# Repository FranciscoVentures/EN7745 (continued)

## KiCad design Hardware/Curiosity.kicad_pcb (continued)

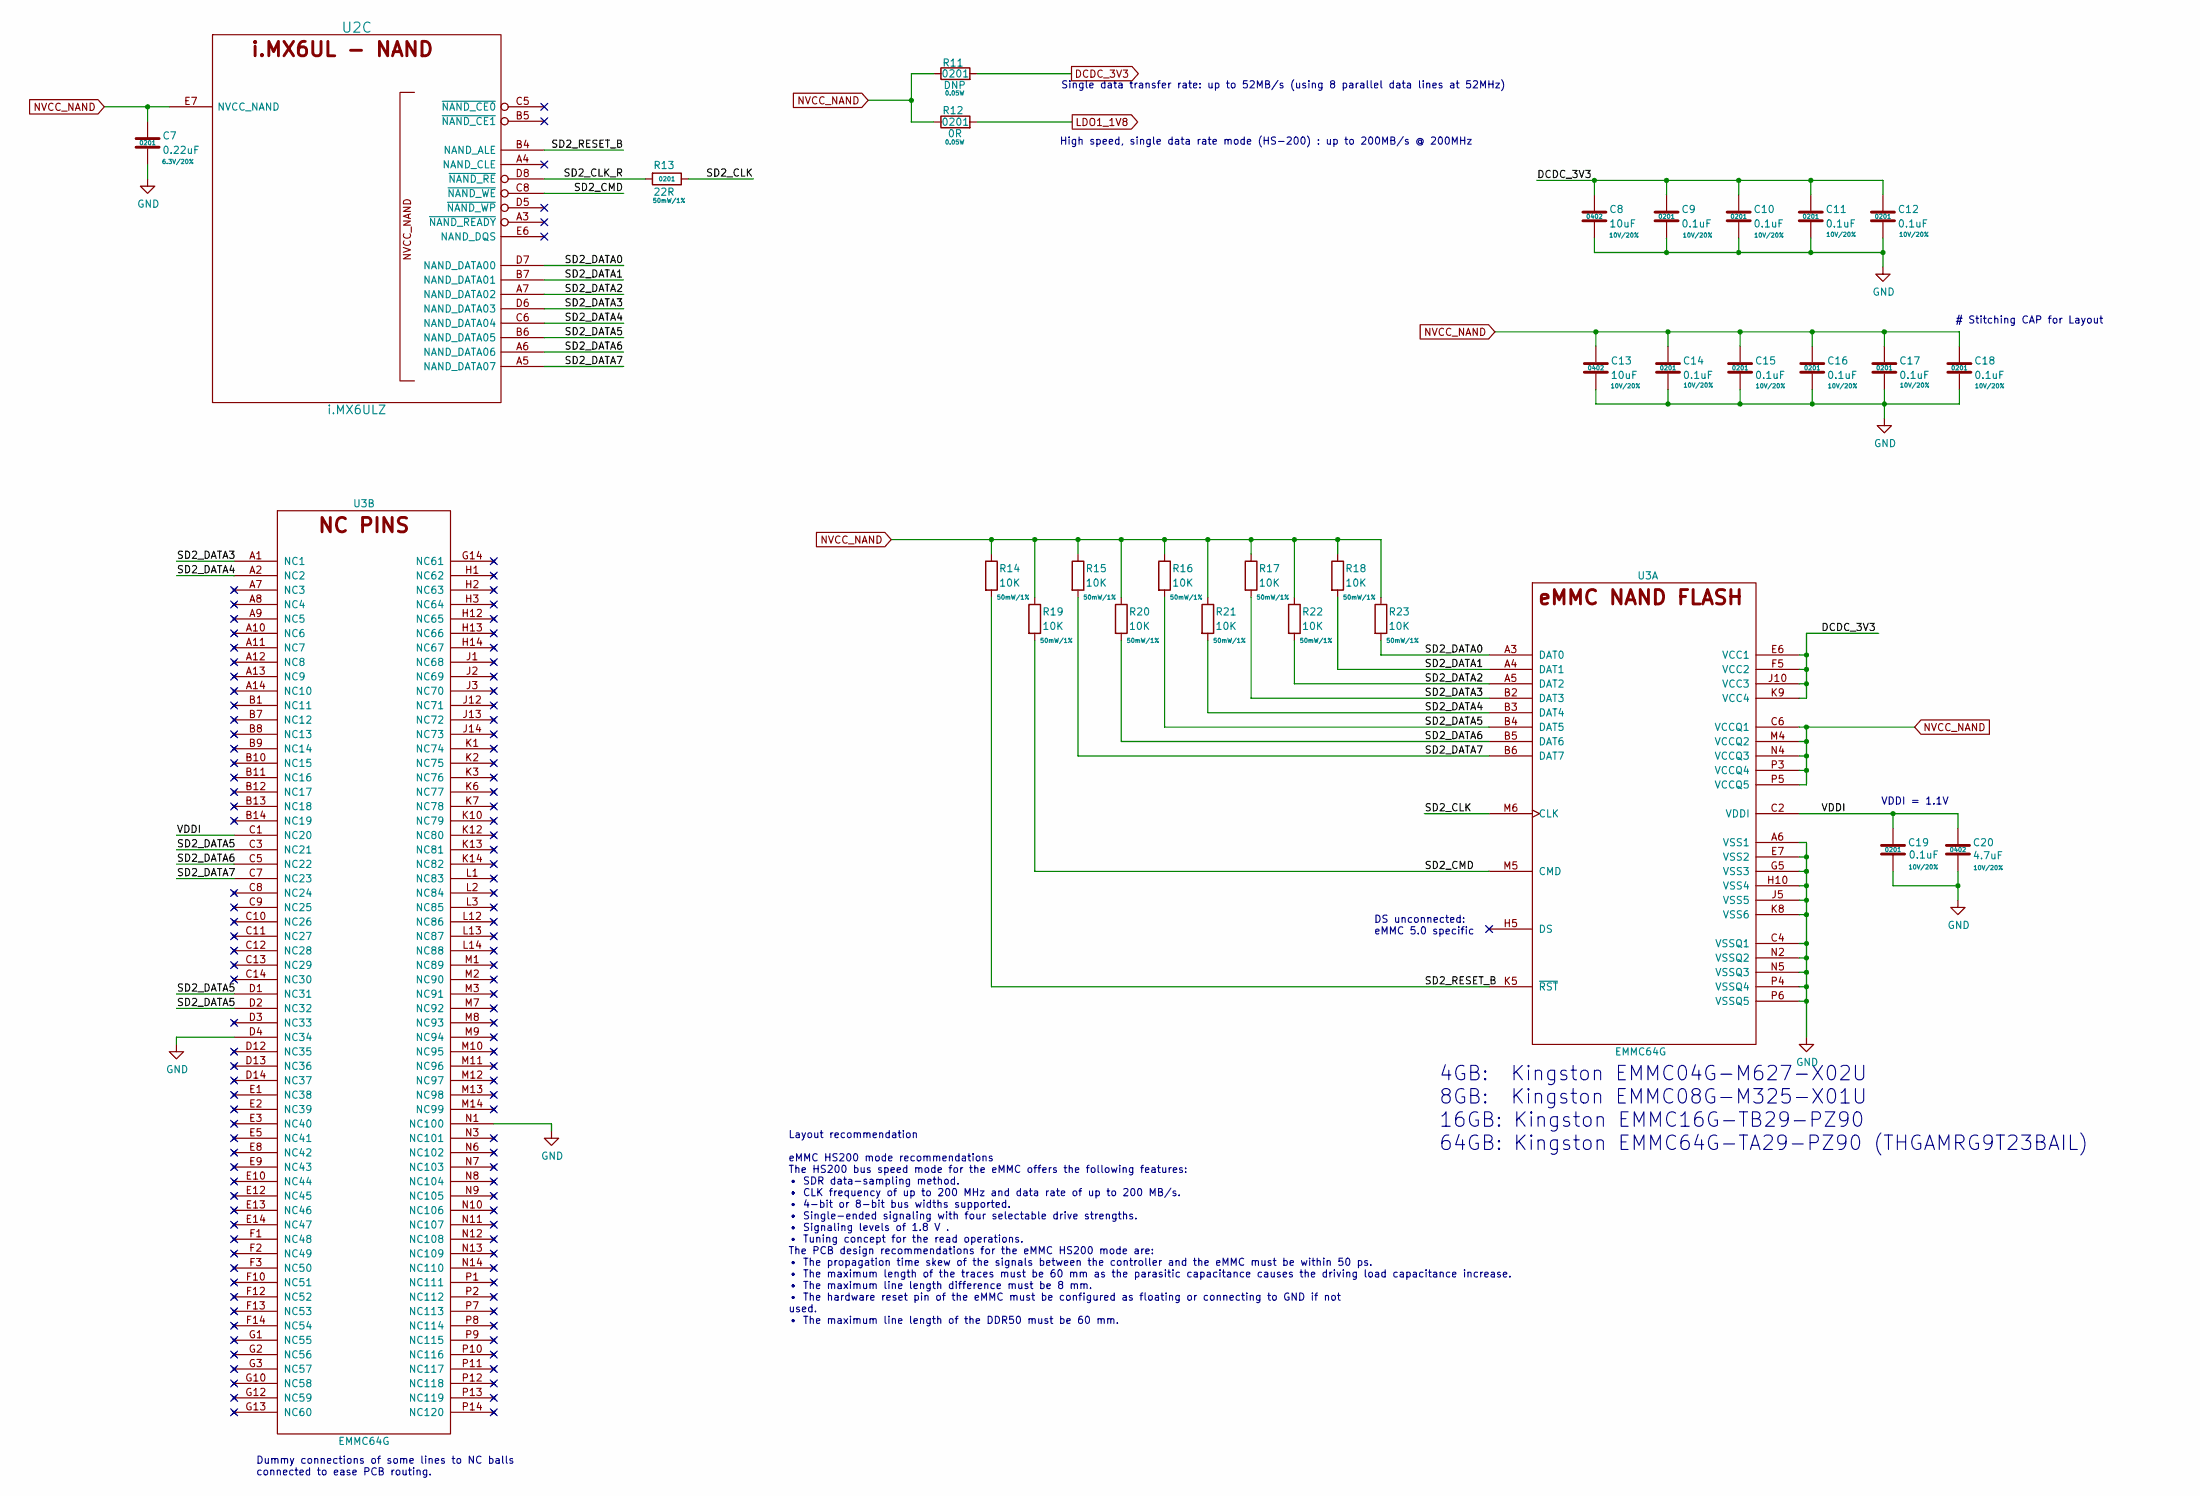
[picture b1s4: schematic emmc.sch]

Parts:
C7: 0.22uF; SM0201; Rating 6.3V/20%; Mfg PN GRM033R60J224ME15D; Digi-Key_PN 490-10407-1-ND
C8, C13: 10uF; SM0402; Rating 10V/20%; Mfg PN CL05A106MP8NUB8; Digi-Key_PN 1276-6830-1-ND
C9, C10, C11, C12, C14, C15, C16, C17, C18, C19: 0.1uF; SM0201; Rating 10V/20%; Mfg PN GRM033R61A104ME15D; Digi-Key_PN 490-5405-1-ND
C20: 4.7uF; SM0402; Rating 10V/20%; Mfg PN ZRB15XR61A475ME01D; Digi-Key_PN 490-10984-1-ND
R11: DNP; R_0201_0603Metric; Rating 0.05W; Mfg PN CRCW02010000Z0ED; Digi-Key_PN 541-0.0AGCT-ND
R12: 0R; R_0201_0603Metric; Rating 0.05W; Mfg PN CRCW02010000Z0ED; Digi-Key_PN 541-0.0AGCT-ND
R13: 22R; R_0201_0603Metric; Rating 50mW/1%; Mfg PN CRCW020122R0JNED; Digi-Key_PN 541-22AGCT-ND
R14, R15, R16, R17, R18, R19, R20, R21, R22, R23: 10K; R_0201_0603Metric; Rating 50mW/1%; Mfg PN CRCW020110K0JNED; Digi-Key_PN 541-10KAGCT-ND
U2: i.MX6ULZ; SOT1534-2; Mfg PN MCIMX6Z0DVM09AB; Digi-Key_PN 568-14726-ND
U3: EMMC64G; FBGA-153; Mfg PN THGAMRG9T23BAIL; Digi-Key_PN THGAMRG9T23BAIL-ND

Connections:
/eMMC/SD2_CLK: R13.1, U3.M6 (CLK)
/eMMC/SD2_CLK_R: R13.2, U2.D8 (~NAND_RE); also elsewhere on the board
/eMMC/SD2_CMD: R19.2, U2.C8 (~NAND_WE), U3.M5 (CMD); also elsewhere on the board
/eMMC/SD2_DATA0: R23.2, U2.D7 (NAND_DATA00), U3.A3 (DAT0); also elsewhere on the board
/eMMC/SD2_DATA1: R18.2, U2.B7 (NAND_DATA01), U3.A4 (DAT1); also elsewhere on the board
/eMMC/SD2_DATA2: R22.2, U2.A7 (NAND_DATA02), U3.A5 (DAT2); also elsewhere on the board
/eMMC/SD2_DATA3: R17.2, U2.D6 (NAND_DATA03), U3.A1 (NC1), U3.B2 (DAT3); also elsewhere on the board
/eMMC/SD2_DATA4: R21.2, U2.C6 (NAND_DATA04), U3.A2 (NC2), U3.B3 (DAT4); also elsewhere on the board
/eMMC/SD2_DATA5: R16.2, U2.B6 (NAND_DATA05), U3.B4 (DAT5), U3.C3 (NC21), U3.D1 (NC31), U3.D2 (NC32); also elsewhere on the board
/eMMC/SD2_DATA6: R20.2, U2.A6 (NAND_DATA06), U3.B5 (DAT6), U3.C5 (NC22); also elsewhere on the board
/eMMC/SD2_DATA7: R15.2, U2.A5 (NAND_DATA07), U3.B6 (DAT7), U3.C7 (NC23); also elsewhere on the board
/eMMC/SD2_RESET_B: R14.2, U2.B4 (NAND_ALE), U3.K5 (~RST); also elsewhere on the board
/eMMC/VDDI: C19.1, C20.1, U3.C1 (NC20), U3.C2 (VDDI)
DCDC_3V3: C8.1, C9.1, C10.1, C11.1, C12.1, R11.2, U3.E6 (VCC1), U3.F5 (VCC2), U3.J10 (VCC3), U3.K9 (VCC4); also elsewhere on the board
GND: C7.2, C8.2, C9.2, C10.2, C11.2, C12.2, C13.2, C14.2, C15.2, C16.2, C17.2, C18.2, C19.2, C20.2, U3.A6 (VSS1), U3.C4 (VSSQ1), U3.D4 (NC34), U3.E7 (VSS2), U3.G5 (VSS3), U3.H10 (VSS4), U3.J5 (VSS5), U3.K8 (VSS6), U3.N1 (NC100), U3.N2 (VSSQ2), U3.N5 (VSSQ3), U3.P4 (VSSQ4), U3.P6 (VSSQ5); also elsewhere on the board
LDO1_1V8: R12.2; also elsewhere on the board
NVCC_NAND: C7.1, C13.1, C14.1, C15.1, C16.1, C17.1, C18.1, R11.1, R12.1, R14.1, R15.1, R16.1, R17.1, R18.1, R19.1, R20.1, R21.1, R22.1, R23.1, U2.E7 (NVCC_NAND), U3.C6 (VCCQ1), U3.M4 (VCCQ2), U3.N4 (VCCQ3), U3.P3 (VCCQ4), U3.P5 (VCCQ5); also elsewhere on the board
unnamed 175: U2.A3 (~NAND_READY); also elsewhere on the board
unnamed 176: U2.A4 (NAND_CLE); also elsewhere on the board
unnamed 182: U2.B5 (~NAND_CE1); also elsewhere on the board
unnamed 187: U2.C5 (~NAND_CE0); also elsewhere on the board
unnamed 192: U2.D5 (~NAND_WP); also elsewhere on the board
unnamed 196: U2.E6 (NAND_DQS); also elsewhere on the board

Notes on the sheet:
Dummy connections of some lines to NC balls connected to ease PCB routing.
DS unconnected: eMMC 5.0 specific
4GB: Kingston EMMC04G-M627-X02U 8GB: Kingston EMMC08G-M325-X01U 16GB: Kingston EMMC16G-TB29-PZ90 64GB: Kingston EMMC64G-TA29-PZ90 (THGAMRG9T23BAIL)
# Stitching CAP for Layout
High speed, single data rate mode (HS-200) : up to 200MB/s @ 200MHz
Single data transfer rate: up to 52MB/s (using 8 parallel data lines at 52MHz)
Layout recommendation eMMC HS200 mode recommendations The HS200 bus speed mode for the eMMC offers the following features: • SDR data-sampling method. • CLK frequency of up to 200 MHz and data rate of up to 200 MB/s. • 4-bit or 8-bit bus widths supported. • Single-ended signaling with four selectab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
VDDI = 1.1V

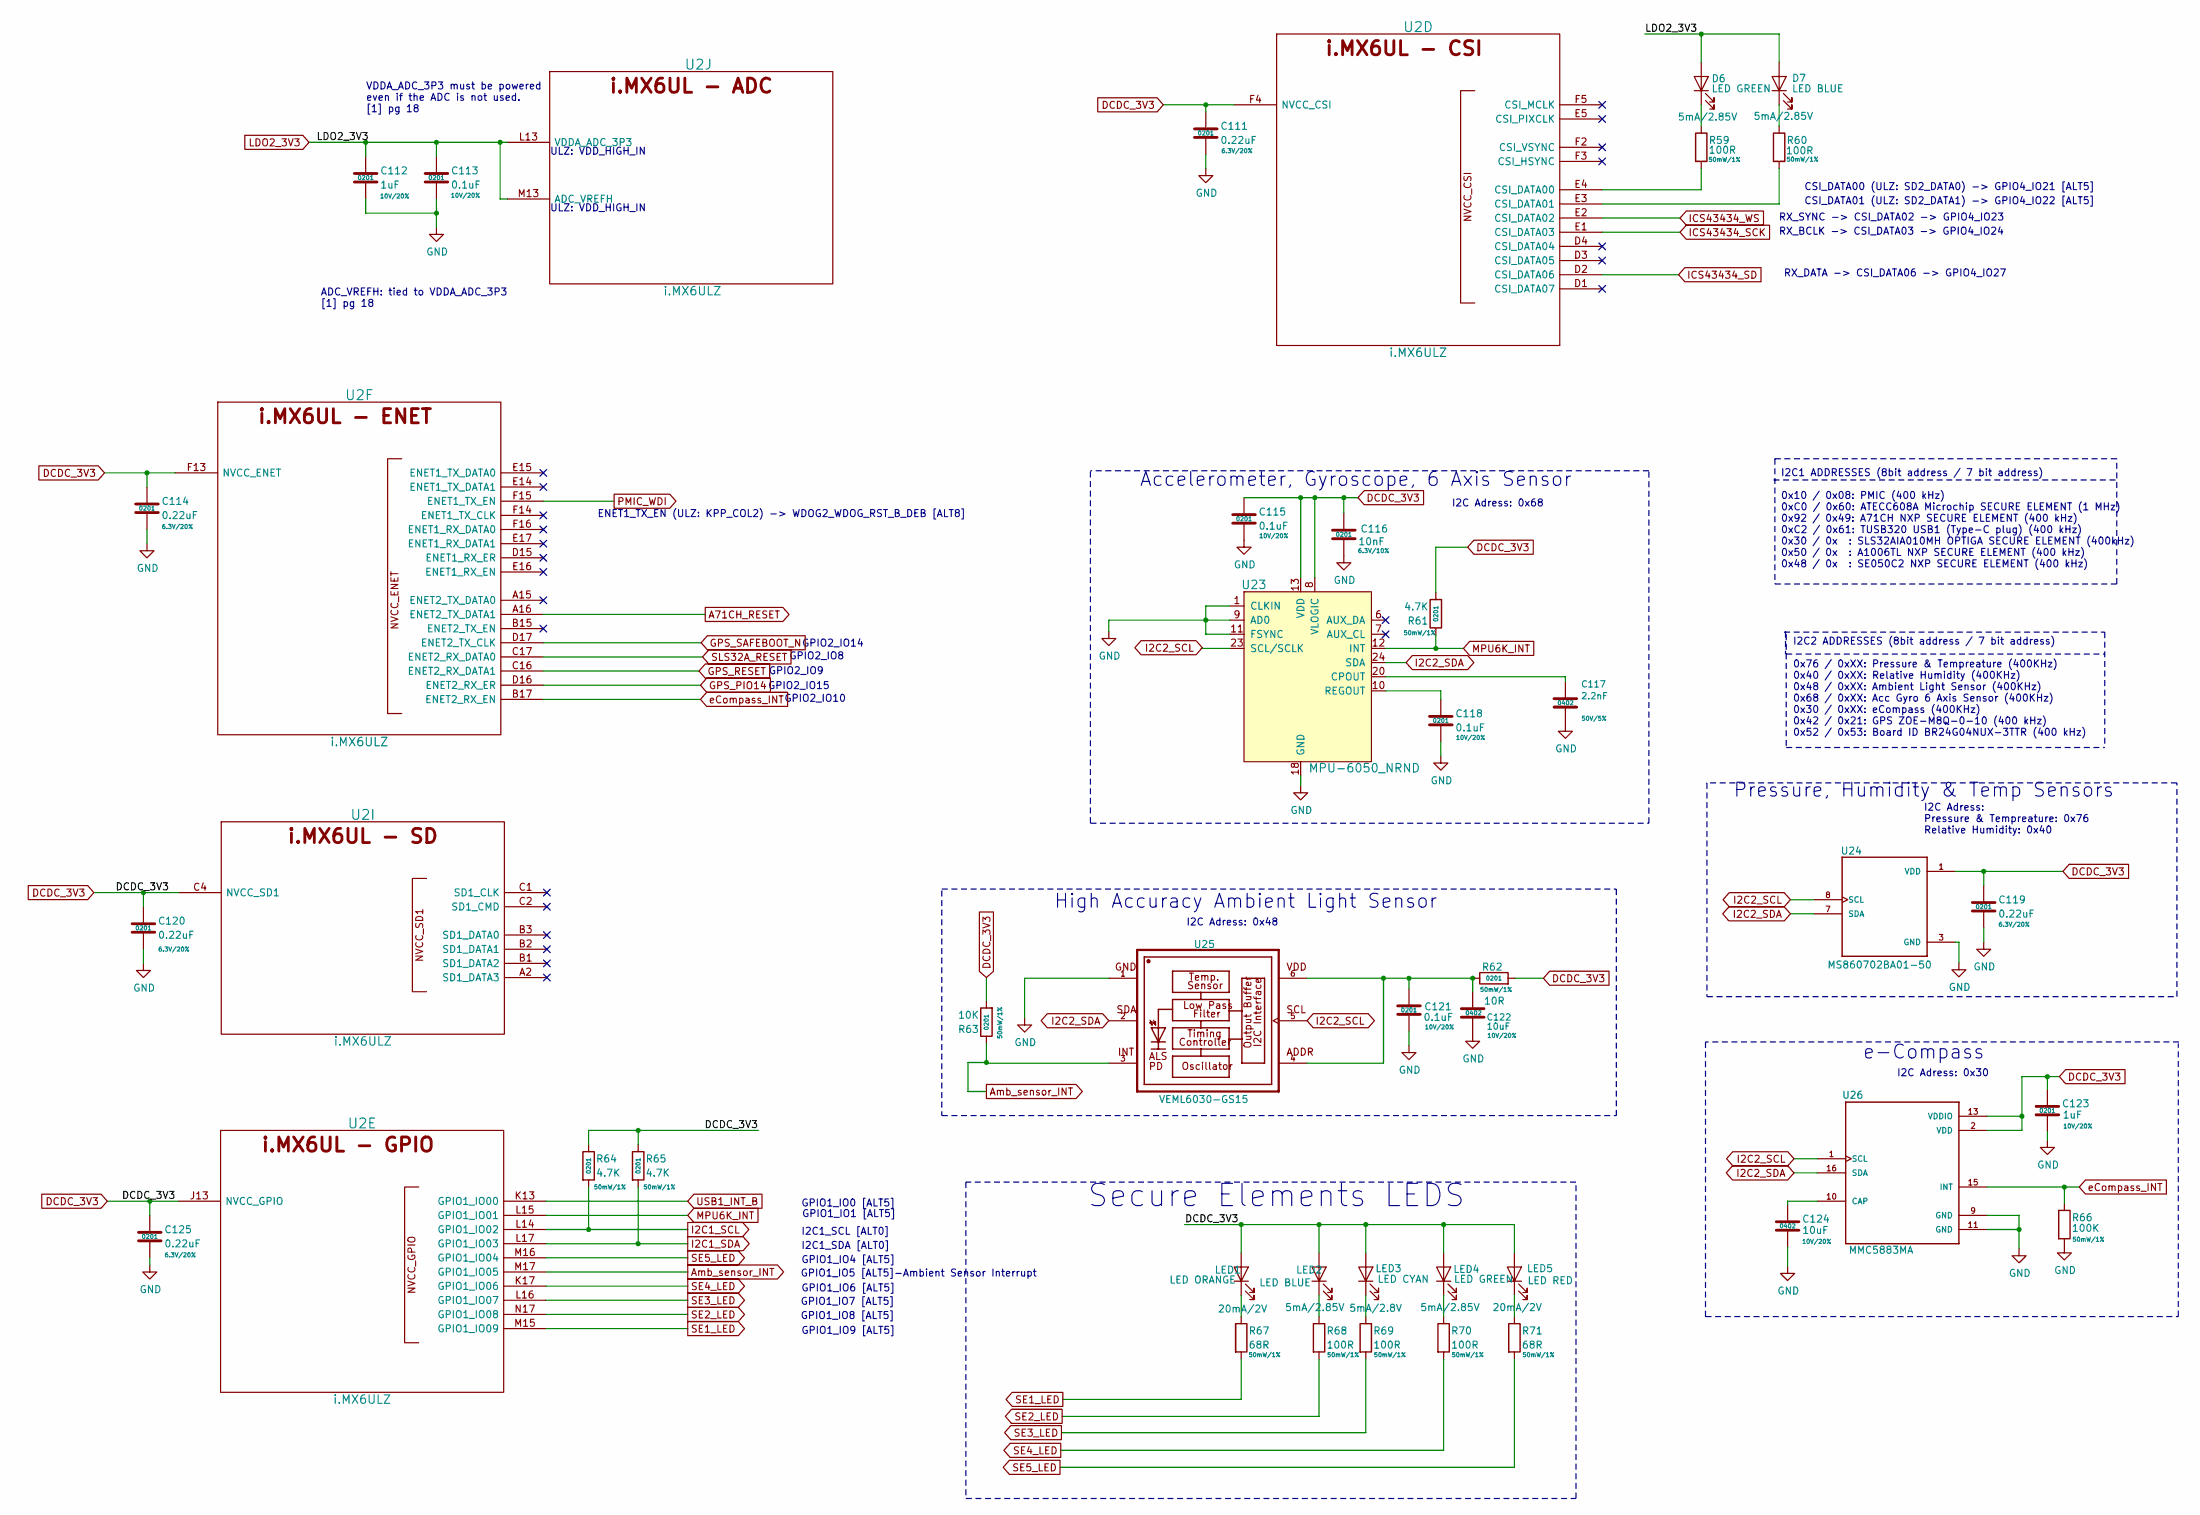
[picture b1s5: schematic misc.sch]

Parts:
C111, C114, C119, C120, C125: 0.22uF; SM0201; Rating 6.3V/20%; Mfg PN GRM033R60J224ME15D; Digi-Key_PN 490-10407-1-ND
C112, C123: 1uF; SM0201; Rating 10V/20%; Mfg PN CL03A105MP3ZSNH; Digi-Key_PN 1276-6816-1-ND
C113, C115, C118, C121: 0.1uF; SM0201; Rating 10V/20%; Mfg PN GRM033R61A104ME15D; Digi-Key_PN 490-5405-1-ND
C116: 10nF; SM0201; Rating 6.3V/10%; Mfg PN GRM033R70J103KA01D; Digi-Key_PN 490-1262-1-ND
C117: 2.2nF; C_0402_1005Metric; Rating 50V/5%; Mfg PN GRM155R71H222JA01J; Digi-Key_PN 490-6359-1-ND
C122: 10uF; C_0402_1005Metric; Rating 10V/20%; Mfg PN CL05A106MP8NUB8; Digi-Key_PN 1276-6830-1-ND
C124: 10uF; SM0402; Rating 10V/20%; Mfg PN CL05A106MP8NUB8; Digi-Key_PN 1276-6830-1-ND
D6: LED GREEN; LED_0603; Rating 5mA/2.85V; Mfg PN LT Q39G-Q1OO-25-1; Digi-Key_PN 475-3442-1-ND
D7: LED BLUE; SM0603_LED; Rating 5mA/2.85V; Mfg PN LB Q39G-L2OO-35-1; Digi-Key_PN 475-2816-1-ND
LED1: LED ORANGE; LED_0603; Rating 20mA/2V; Mfg PN LO Q976-PS-25-0-20-R18; Digi-Key_PN 475-2486-1-ND
LED2: LED BLUE; LED_0603; Rating 5mA/2.85V; Mfg PN LB Q39G-L2OO-35-1; Digi-Key_PN 475-2816-1-ND
LED3: LED CYAN; LED_0603; Rating 5mA/2.8V; Mfg PN APT1608VRCXF/A-5MAV; Digi-Key_PN 754-2180-1-ND
LED4: LED GREEN; LED_0603; Rating 5mA/2.85V; Mfg PN LT Q39G-Q1OO-25-1; Digi-Key_PN 475-3442-1-ND
LED5: LED RED; LED_0603; Rating 20mA/2V; Mfg PN LS Q976-NR-1; Digi-Key_PN 475-2512-1-ND
R59, R60, R68, R69, R70: 100R; R_0201_0603Metric; Rating 50mW/1%; Mfg PN CRCW0201100RFNED; Digi-Key_PN 541-100ABCT-ND
R61, R64, R65: 4.7K; R_0201_0603Metric; Rating 50mW/1%; Mfg PN CRCW02014K70JNED; Digi-Key_PN 541-4.7KAGCT-ND
R62: 10R; R_0201_0603Metric; Rating 50mW/1%; Mfg PN CRCW020110R0FNED; Digi-Key_PN 541-10.0ABCT-ND
R63: 10K; R_0201_0603Metric; Rating 50mW/1%; Mfg PN CRCW020110K0JNED; Digi-Key_PN 541-10KAGCT-ND
R66: 100K; R_0201_0603Metric; Rating 50mW/1%; Mfg PN CRCW0201100KJNED; Digi-Key_PN 541-100KAGCT-ND
R67, R71: 68R; R_0201_0603Metric; Rating 50mW/1%; Mfg PN CRCW020168R0FNED; Digi-Key_PN 541-CRCW020168R0FNEDCT-ND
U2: i.MX6ULZ; SOT1534-2; Mfg PN MCIMX6Z0DVM09AB; Digi-Key_PN 568-14726-ND
U23: MPU-6050_NRND; QFN-24-1EP_4x4mm; Mfg PN MPU-6050; Digi-Key_PN 1428-1007-1-ND
U24: MS860702BA01-50; TE_MS860702BA01-50; Mfg PN MS860702BA01-50; Digi-Key_PN 223-1701-1-ND
U25: VEML6030-GS15; VISHAY_VEML6030_2X2X0.87; Mfg PN VEML6030-GS15; Digi-Key_PN VEML6030-GS15CT-ND
U26: MMC5883MA; PQFN50P300X300X100-16N; Mfg PN MMC5883MA; Digi-Key_PN 1267-1072-1-ND

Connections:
A71CH_RESET: U2.A16 (ENET2_TX_DATA1); also elsewhere on the board
Amb_sensor_INT: R63.1, U2.M17 (GPIO1_IO05), U25.3; also elsewhere on the board
DCDC_3V3: C111.1, C114.1, C115.1, C116.1, C119.1, C120.1, C123.1, C125.1, LED1.2 (A), LED2.2 (A), LED3.2 (A), LED4.2 (A), LED5.2 (A), R61.2, R62.2, R63.2, R64.1, R65.1, U2.C4 (NVCC_SD1), U2.F4 (NVCC_CSI), U2.F13 (NVCC_ENET), U2.J13 (NVCC_GPIO), U23.8 (VLOGIC), U23.13 (VDD), U24.1 (VDD), U26.2 (VDD), U26.13 (VDDIO); also elsewhere on the board
GND: C111.2, C112.2, C113.2, C114.2, C115.2, C116.2, C117.2, C118.2, C119.2, C120.2, C121.2, C122.2, C123.2, C124.2, C125.2, R66.2, U23.1 (CLKIN), U23.9 (AD0), U23.11 (FSYNC), U23.18 (GND), U24.3 (GND), U25.1, U26.9 (GND), U26.11 (GND); also elsewhere on the board
GPS_PIO14: U2.D16 (ENET2_RX_ER); also elsewhere on the board
GPS_RESET: U2.C16 (ENET2_RX_DATA1); also elsewhere on the board
GPS_SAFEBOOT_N: U2.D17 (ENET2_TX_CLK); also elsewhere on the board
I2C1_SCL: R64.2, U2.L14 (GPIO1_IO02); also elsewhere on the board
I2C1_SDA: R65.2, U2.L17 (GPIO1_IO03); also elsewhere on the board
I2C2_SCL: U23.23 (SCL/SCLK), U24.8 (SCL), U25.5, U26.1 (SCL); also elsewhere on the board
I2C2_SDA: U23.24 (SDA), U24.7 (SDA), U25.2, U26.16 (SDA); also elsewhere on the board
ICS43434_SCK: U2.E1 (CSI_DATA03); also elsewhere on the board
ICS43434_SD: U2.D2 (CSI_DATA06); also elsewhere on the board
ICS43434_WS: U2.E2 (CSI_DATA02); also elsewhere on the board
LDO2_3V3: C112.1, C113.1, D6.2 (A), D7.2 (A), U2.L13 (VDDA_ADC_3P3), U2.M13 (ADC_VREFH); also elsewhere on the board
MPU6K_INT: R61.1, U2.L15 (GPIO1_IO01), U23.12 (INT); also elsewhere on the board
unnamed: C117.1, U23.20 (CPOUT)
unnamed: C118.1, U23.10 (REGOUT)
unnamed: C121.1, C122.1, R62.1, U25.4, U25.6
unnamed: C124.1, U26.10 (CAP)
unnamed: D6.1 (K), R59.1
unnamed: D7.1 (K), R60.1
unnamed: LED1.1 (K), R67.1
unnamed: LED2.1 (K), R68.1
unnamed: LED3.1 (K), R69.1
unnamed: LED4.1 (K), R70.1
unnamed: LED5.1 (K), R71.1
unnamed 172: R59.2, U2.E4 (CSI_DATA00); also elsewhere on the board
unnamed 173: R60.2, U2.E3 (CSI_DATA01); also elsewhere on the board
unnamed 174: U2.A2 (SD1_DATA3); also elsewhere on the board
unnamed 178: U2.A15 (ENET2_TX_DATA0); also elsewhere on the board
unnamed 179: U2.B1 (SD1_DATA2); also elsewhere on the board
unnamed 180: U2.B2 (SD1_DATA1); also elsewhere on the board
unnamed 181: U2.B3 (SD1_DATA0); also elsewhere on the board
unnamed 184: U2.B15 (ENET2_TX_EN); also elsewhere on the board
unnamed 185: U2.C1 (SD1_CLK); also elsewhere on the board
unnamed 186: U2.C2 (SD1_CMD); also elsewhere on the board
unnamed 189: U2.D1 (CSI_DATA07); also elsewhere on the board
unnamed 190: U2.D3 (CSI_DATA05); also elsewhere on the board
unnamed 191: U2.D4 (CSI_DATA04); also elsewhere on the board
unnamed 194: U2.D15 (ENET1_RX_ER); also elsewhere on the board
unnamed 195: U2.E5 (CSI_PIXCLK); also elsewhere on the board
unnamed 198: U2.E14 (ENET1_TX_DATA1); also elsewhere on the board
unnamed 199: U2.E15 (ENET1_TX_DATA0); also elsewhere on the board
unnamed 200: U2.E16 (ENET1_RX_EN); also elsewhere on the board
unnamed 201: U2.E17 (ENET1_RX_DATA1); also elsewhere on the board
unnamed 203: U2.F2 (CSI_VSYNC); also elsewhere on the board
unnamed 204: U2.F3 (CSI_HSYNC); also elsewhere on the board
unnamed 205: U2.F5 (CSI_MCLK); also elsewhere on the board
unnamed 206: U2.F14 (ENET1_TX_CLK); also elsewhere on the board
unnamed 207: U2.F16 (ENET1_RX_DATA0); also elsewhere on the board
PMIC_WDI: U2.F15 (ENET1_TX_EN); also elsewhere on the board
SE1_LED: R67.2, U2.M15 (GPIO1_IO09); also elsewhere on the board
SE2_LED: R68.2, U2.N17 (GPIO1_IO08); also elsewhere on the board
SE3_LED: R69.2, U2.L16 (GPIO1_IO07); also elsewhere on the board
SE4_LED: R70.2, U2.K17 (GPIO1_IO06); also elsewhere on the board
SE5_LED: R71.2, U2.M16 (GPIO1_IO04); also elsewhere on the board
SLS32A_RESET: U2.C17 (ENET2_RX_DATA0); also elsewhere on the board
USB1_INT_B: U2.K13 (GPIO1_IO00); also elsewhere on the board
eCompass_INT: R66.1, U2.B17 (ENET2_RX_EN), U26.15 (INT); also elsewhere on the board

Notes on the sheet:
ADC_VREFH: tied to VDDA_ADC_3P3 [1] pg 18
VDDA_ADC_3P3 must be powered even if the ADC is not used. [1] pg 18
I2C1_SCL [ALT0]
I2C1_SDA [ALT0]
GPIO1_IO9 [ALT5]
GPIO1_IO6 [ALT5]
GPIO1_IO4 [ALT5]
I2C1 ADDRESSES (8bit address / 7 bit address) 0x10 / 0x08: PMIC (400 kHz) 0xC0 / 0x60: ATECC608A Microchip SECURE ELEMENT (1 MHz) 0x92 / 0x49: A71CH NXP SECURE ELEMENT (400 kHz) 0xC2 / 0x61: TUSB320 USB1 (Type-C plug) (400 kHz) 0x30 / 0x : SLS32AIA010MH OPTIGA SECURE ELEMENT (400kHz) 0x50 / 0x : A1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
GPIO1_IO0 [ALT5]
ENET1_TX_EN (ULZ: KPP_COL2) -> WDOG2_WDOG_RST_B_DEB [ALT8]
CSI_DATA00 (ULZ: SD2_DATA0) -> GPIO4_IO21 [ALT5]
CSI_DATA01 (ULZ: SD2_DATA1) -> GPIO4_IO22 [ALT5]
ULZ: VDD_HIGH_IN
Secure Elements LEDS
Pressure, Humidity & Temp Sensors
I2C Adress: Pressure & Tempreature: 0x76 Relative Humidity: 0x40
High Accuracy Ambient Light Sensor
I2C Adress: 0x48
GPIO1_IO5 [ALT5]-Ambient Sensor Interrupt
GPIO1_IO7 [ALT5]
GPIO1_IO8 [ALT5]
I2C Adress: 0x68
GPIO1_IO1 [ALT5]
Accelerometer, Gyroscope, 6 Axis Sensor
RX_SYNC -> CSI_DATA02 -> GPIO4_IO23
RX_BCLK -> CSI_DATA03 -> GPIO4_IO24
RX_DATA -> CSI_DATA06 -> GPIO4_IO27
GPIO2_IO8
GPIO2_IO9
GPIO2_IO15
e-Compass
I2C Adress: 0x30
GPIO2_IO14
I2C2 ADDRESSES (8bit address / 7 bit address) 0x76 / 0xXX: Pressure & Tempreature (400KHz) 0x40 / 0xXX: Relative Humidity (400KHz) 0x48 / 0xXX: Ambient Light Sensor (400KHz) 0x68 / 0xXX: Acc Gyro 6 Axis Sensor (400KHz) 0x30 / 0xXX: eCompass (400KHz) 0x42 / 0x21: GPS ZOE-M8Q-0-10 (400 kHz) 0x52 / 0x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
GPIO2_IO10

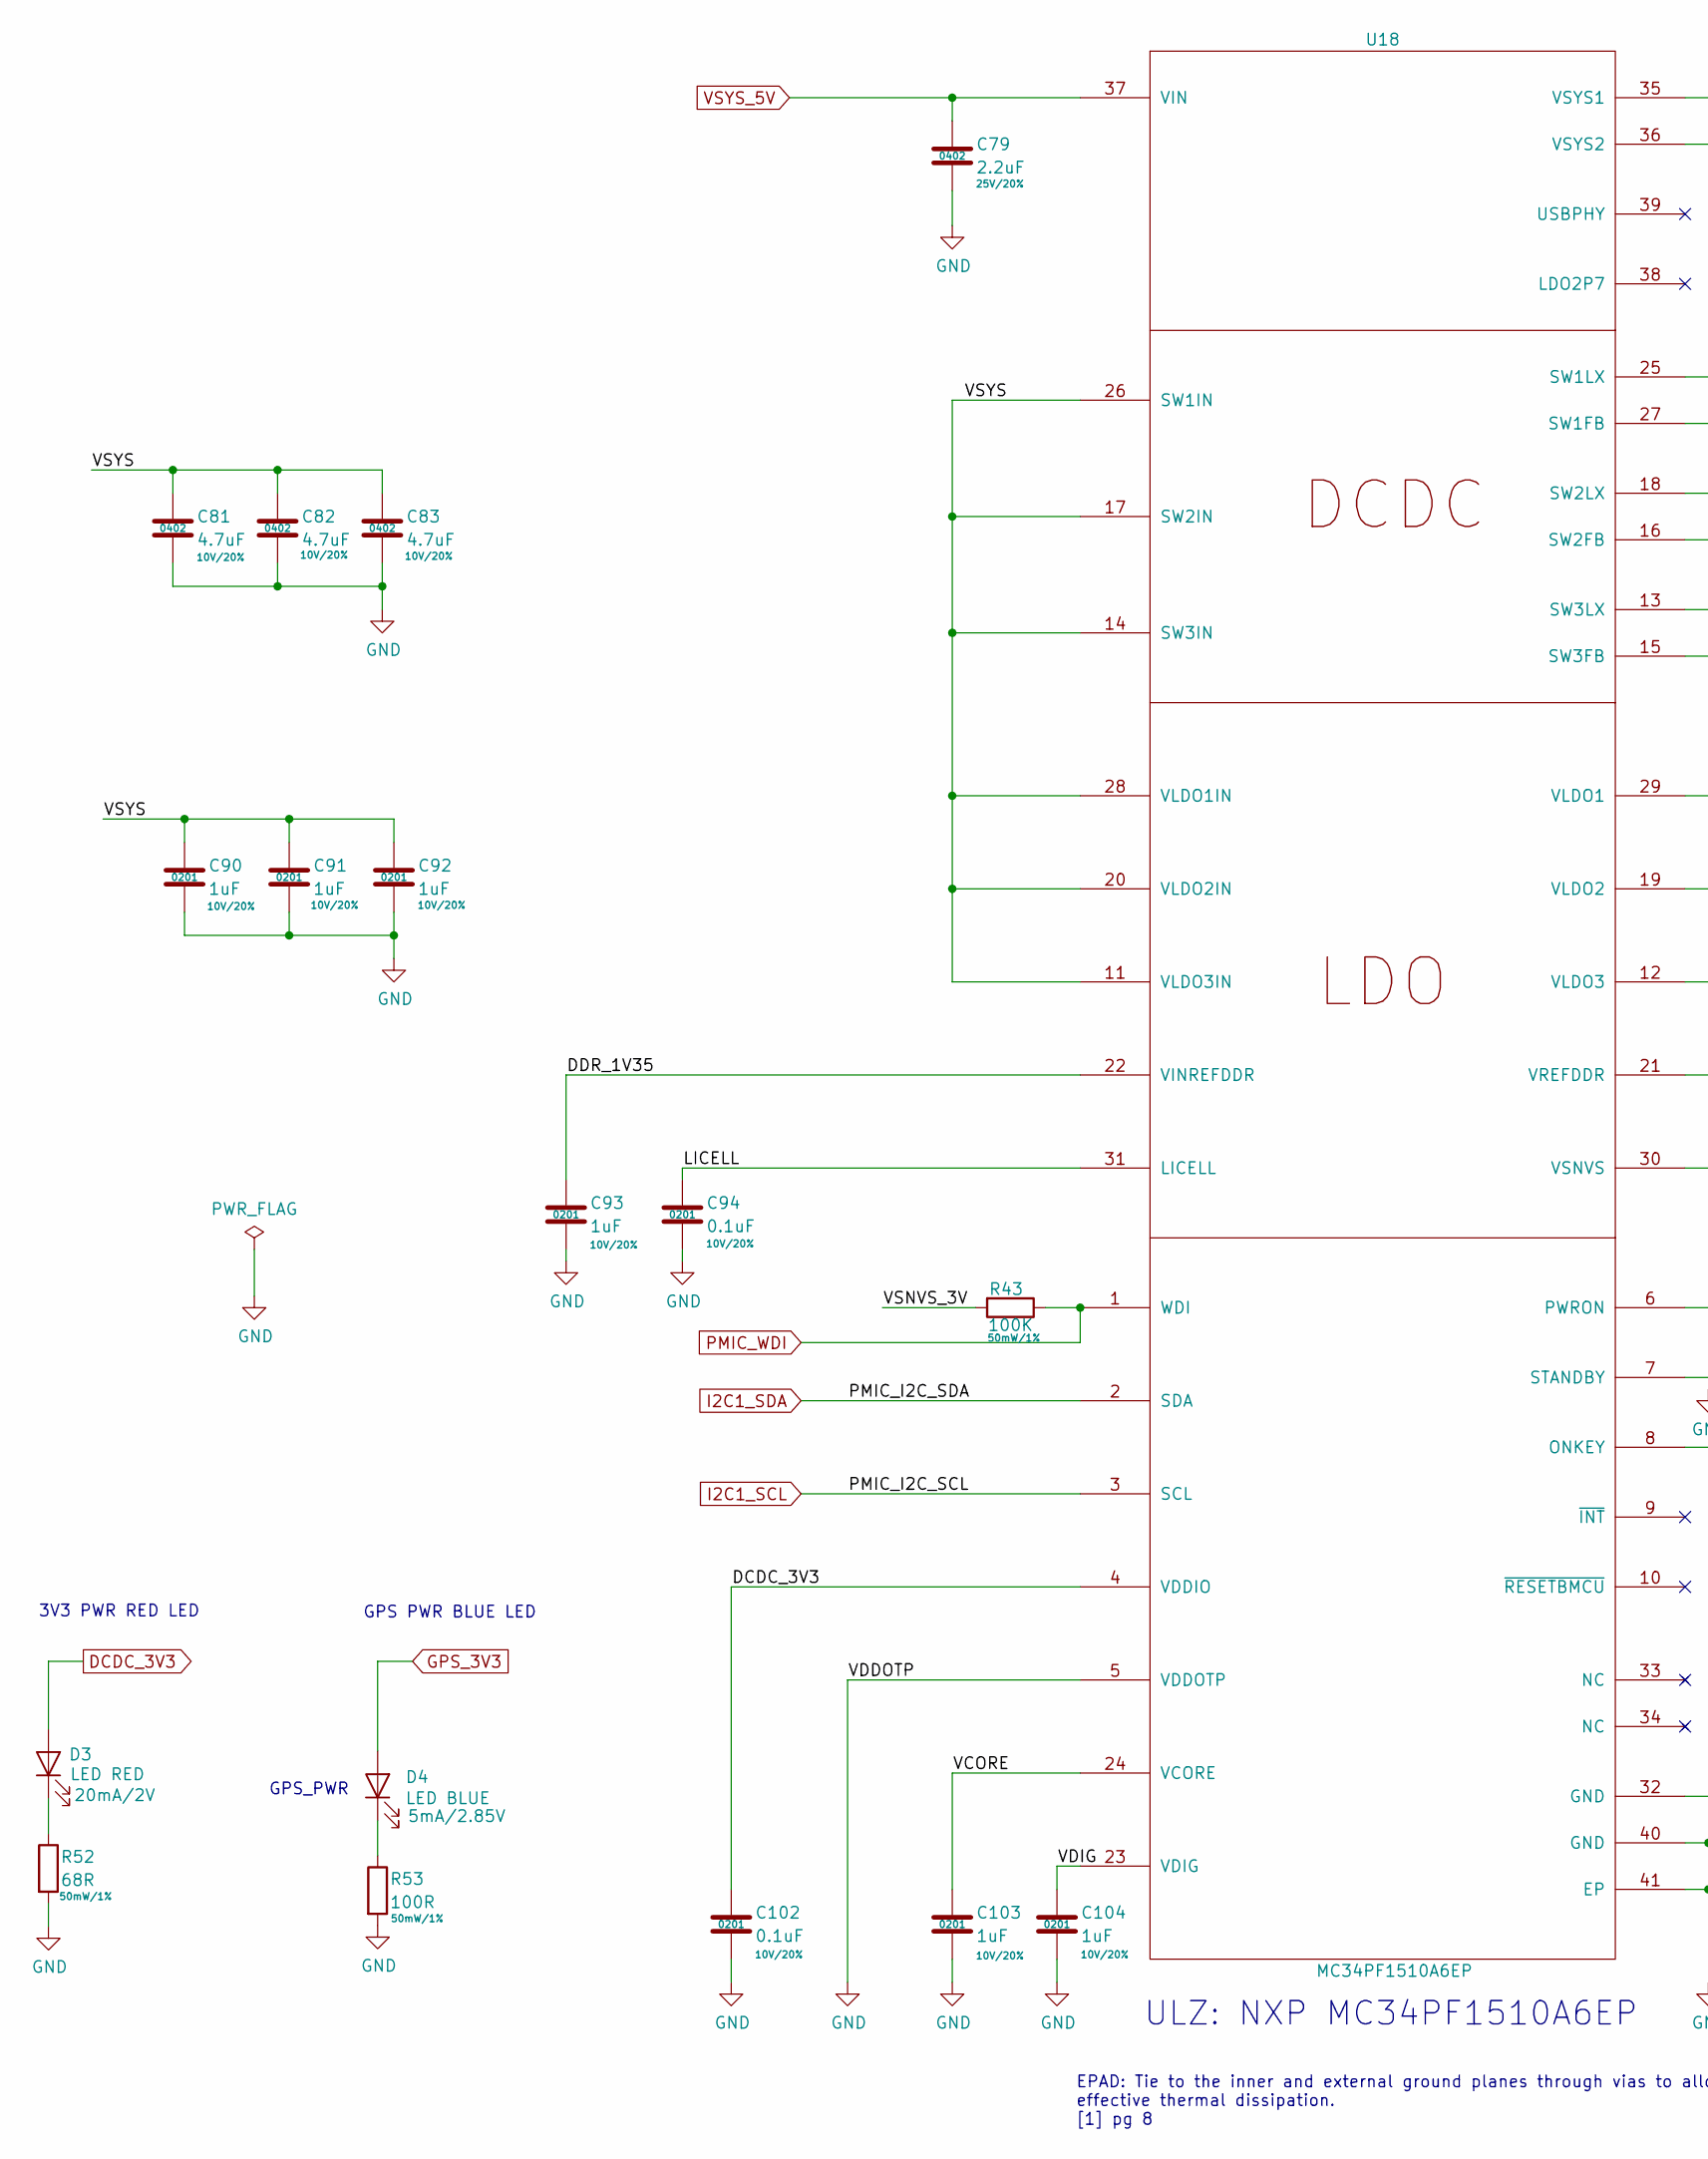
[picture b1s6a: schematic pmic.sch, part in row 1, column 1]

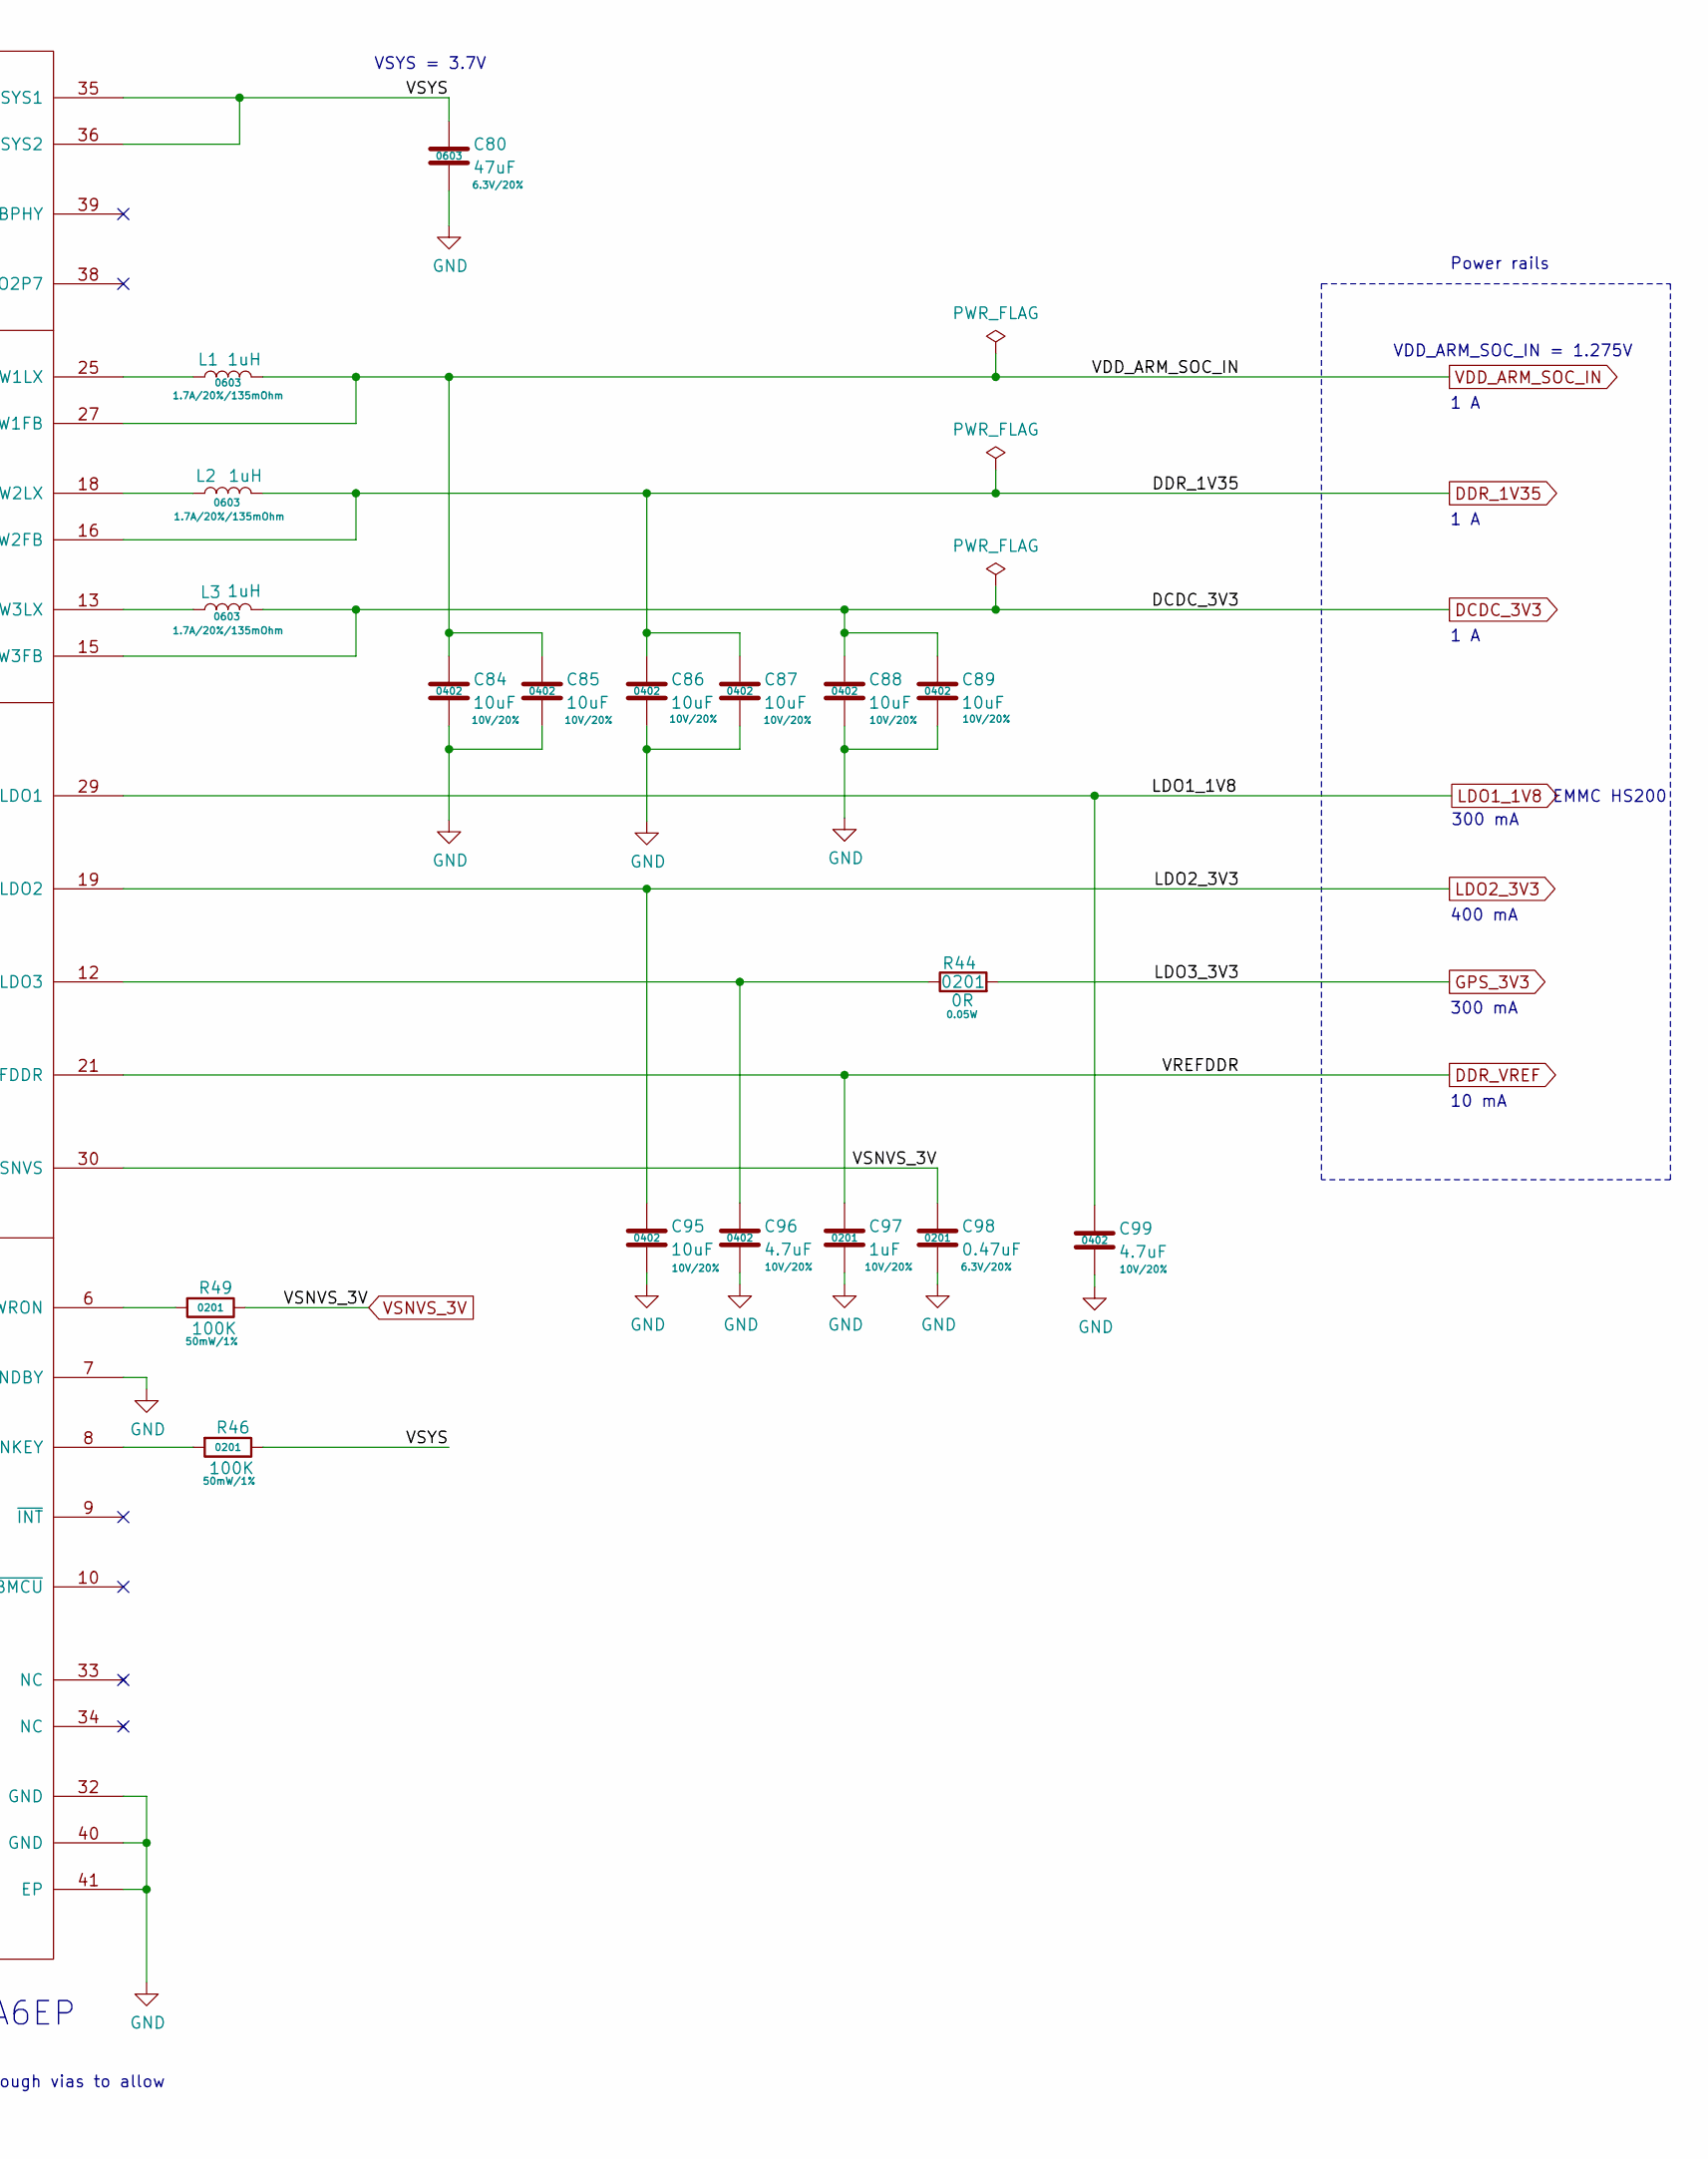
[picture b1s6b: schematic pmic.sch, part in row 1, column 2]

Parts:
C79: 2.2uF; SM0402; Rating 25V/20%; Mfg PN GRM155R61E225ME15D; Digi-Key_PN 490-10457-1-ND
C80: 47uF; SM0603; Rating 6.3V/20%; Mfg PN GRM188R60J476ME15D; Digi-Key_PN 490-13247-1-ND
C81, C82, C83, C96, C99: 4.7uF; SM0402; Rating 10V/20%; Mfg PN ZRB15XR61A475ME01D; Digi-Key_PN 490-10984-1-ND
C84, C85, C86, C87, C88, C89, C95: 10uF; SM0402; Rating 10V/20%; Mfg PN CL05A106MP8NUB8; Digi-Key_PN 1276-6830-1-ND
C90, C91, C92, C93, C97, C103, C104: 1uF; SM0201; Rating 10V/20%; Mfg PN CL03A105MP3ZSNH; Digi-Key_PN 1276-6816-1-ND
C94, C102: 0.1uF; SM0201; Rating 10V/20%; Mfg PN GRM033R61A104ME15D; Digi-Key_PN 490-5405-1-ND
C98: 0.47uF; SM0201; Rating 6.3V/20%; Mfg PN GRM033R60J474ME90D; Digi-Key_PN 490-10410-1-ND
D3: LED RED; LED_0603; Rating 20mA/2V; Mfg PN LS Q976-NR-1; Digi-Key_PN 475-2512-1-ND
D4: LED BLUE; LED_0603; Rating 5mA/2.85V; Mfg PN LB Q39G-L2OO-35-1; Digi-Key_PN 475-2816-1-ND
L1, L2, L3: 1uH; SM0603; Rating 1.7A/20%/135mOhm; Mfg PN LPWI160808H1R0T; Digi-Key_PN F12082CT-ND
R43, R46, R49: 100K; R_0201_0603Metric; Rating 50mW/1%; Mfg PN CRCW0201100KJNED; Digi-Key_PN 541-100KAGCT-ND
R44: 0R; R_0201_0603Metric; Rating 0.05W; Mfg PN CRCW02010000Z0ED; Digi-Key_PN 541-0.0AGCT-ND
R52: 68R; R_0201_0603Metric; Rating 50mW/1%; Mfg PN CRCW020168R0FNED; Digi-Key_PN 541-CRCW020168R0FNEDCT-ND
R53: 100R; R_0201_0603Metric; Rating 50mW/1%; Mfg PN CRCW0201100RFNED; Digi-Key_PN 541-100ABCT-ND
U18: MC34PF1510A6EP; SOT1369-4; Mfg PN MC34PF1510A6EP; Digi-Key_PN 568-14653-1-ND

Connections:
/PMIC/LICELL: C94.1, U18.31 (LICELL)
/PMIC/VCORE: C103.1, U18.24 (VCORE)
/PMIC/VDIG: C104.1, U18.23 (VDIG)
/PMIC/VSYS: C80.1, C81.1, C82.1, C83.1, C90.1, C91.1, C92.1, R46.1, U18.11 (VLDO3IN), U18.14 (SW3IN), U18.17 (SW2IN), U18.20 (VLDO2IN), U18.26 (SW1IN), U18.28 (VLDO1IN), U18.35 (VSYS1), U18.36 (VSYS2)
DCDC_3V3: C88.1, C89.1, C102.1, D3.2 (A), L3.2, U18.4 (VDDIO), U18.15 (SW3FB); also elsewhere on the board
DDR_1V35: C86.1, C87.1, C93.1, L2.2, U18.16 (SW2FB), U18.22 (VINREFDDR); also elsewhere on the board
DDR_VREF: C97.1, U18.21 (VREFDDR); also elsewhere on the board
GND: C79.2, C80.2, C81.2, C82.2, C83.2, C84.2, C85.2, C86.2, C87.2, C88.2, C89.2, C90.2, C91.2, C92.2, C93.2, C94.2, C95.2, C96.2, C97.2, C98.2, C99.2, C102.2, C103.2, C104.2, R52.2, R53.2, U18.5 (VDDOTP), U18.7 (STANDBY), U18.32 (GND), U18.40 (GND), U18.41 (EP); also elsewhere on the board
GPS_3V3: D4.2 (A), R44.2
I2C1_SCL: U18.3 (SCL); also elsewhere on the board
I2C1_SDA: U18.2 (SDA); also elsewhere on the board
LDO1_1V8: C99.1, U18.29 (VLDO1); also elsewhere on the board
LDO2_3V3: C95.1, U18.19 (VLDO2); also elsewhere on the board
unnamed: C96.1, R44.1, U18.12 (VLDO3)
unnamed: D3.1 (K), R52.1
unnamed: D4.1 (K), R53.1
unnamed: L1.1, U18.25 (SW1LX)
unnamed: L2.1, U18.18 (SW2LX)
unnamed: L3.1, U18.13 (SW3LX)
unnamed: R46.2, U18.8 (ONKEY)
unnamed: R49.2, U18.6 (PWRON)
PMIC_WDI: R43.1, U18.1 (WDI); also elsewhere on the board
VDD_ARM_SOC_IN: C84.1, C85.1, L1.2, U18.27 (SW1FB); also elsewhere on the board
VSNVS_3V: C98.1, R43.2, R49.1, U18.30 (VSNVS); also elsewhere on the board
VSYS_5V: C79.1, U18.37 (VIN); also elsewhere on the board

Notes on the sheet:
EPAD: Tie to the inner and external ground planes through vias to allow effective thermal dissipation. [1] pg 8
400 mA
300 mA
1 A
10 mA
Power rails
ULZ: NXP MC34PF1510A6EP
3V3 PWR RED LED
GPS_PWR
GPS PWR BLUE LED
EMMC HS200
VSYS = 3.7V
VDD_ARM_SOC_IN = 1.275V
